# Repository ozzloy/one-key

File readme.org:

(- 153.5 133) 20.5
(- 103 78) 25

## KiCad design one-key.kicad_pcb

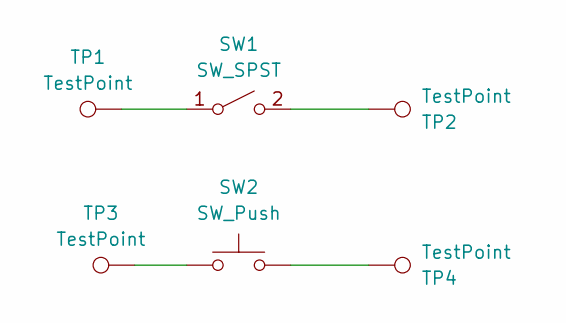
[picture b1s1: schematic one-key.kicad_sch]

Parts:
SW1: SW_SPST; SW_MX_HotSwap_THT
SW2: SW_Push; SW_Kailh_Choc_V1_HotSwap
TP1, TP2, TP3, TP4: TestPoint; TestPoint_Pad_1.0x1.0mm

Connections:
unnamed: SW1.1 (A), TP1.1
unnamed: SW1.2 (B), TP2.1
unnamed: SW2.1, TP3.1
unnamed: SW2.2, TP4.1

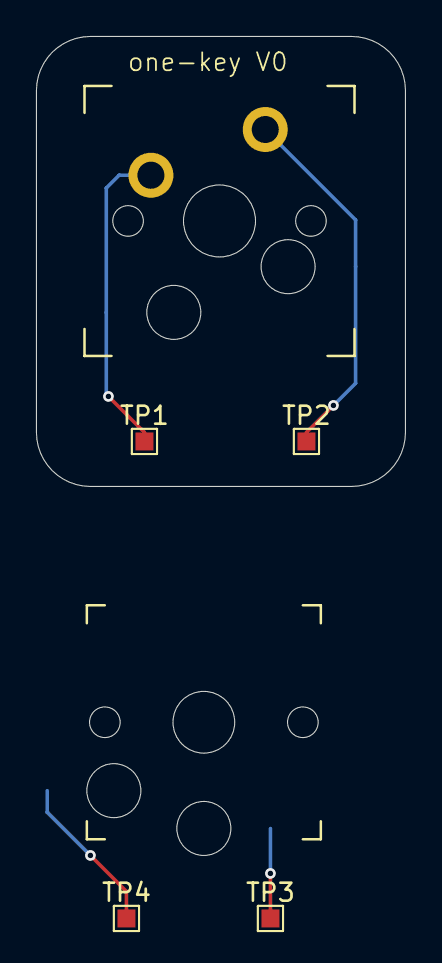
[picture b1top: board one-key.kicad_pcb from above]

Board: 2 copper layers, 20.5 x 25.0 mm, 6 parts (0 on the bottom side), 4 nets.
